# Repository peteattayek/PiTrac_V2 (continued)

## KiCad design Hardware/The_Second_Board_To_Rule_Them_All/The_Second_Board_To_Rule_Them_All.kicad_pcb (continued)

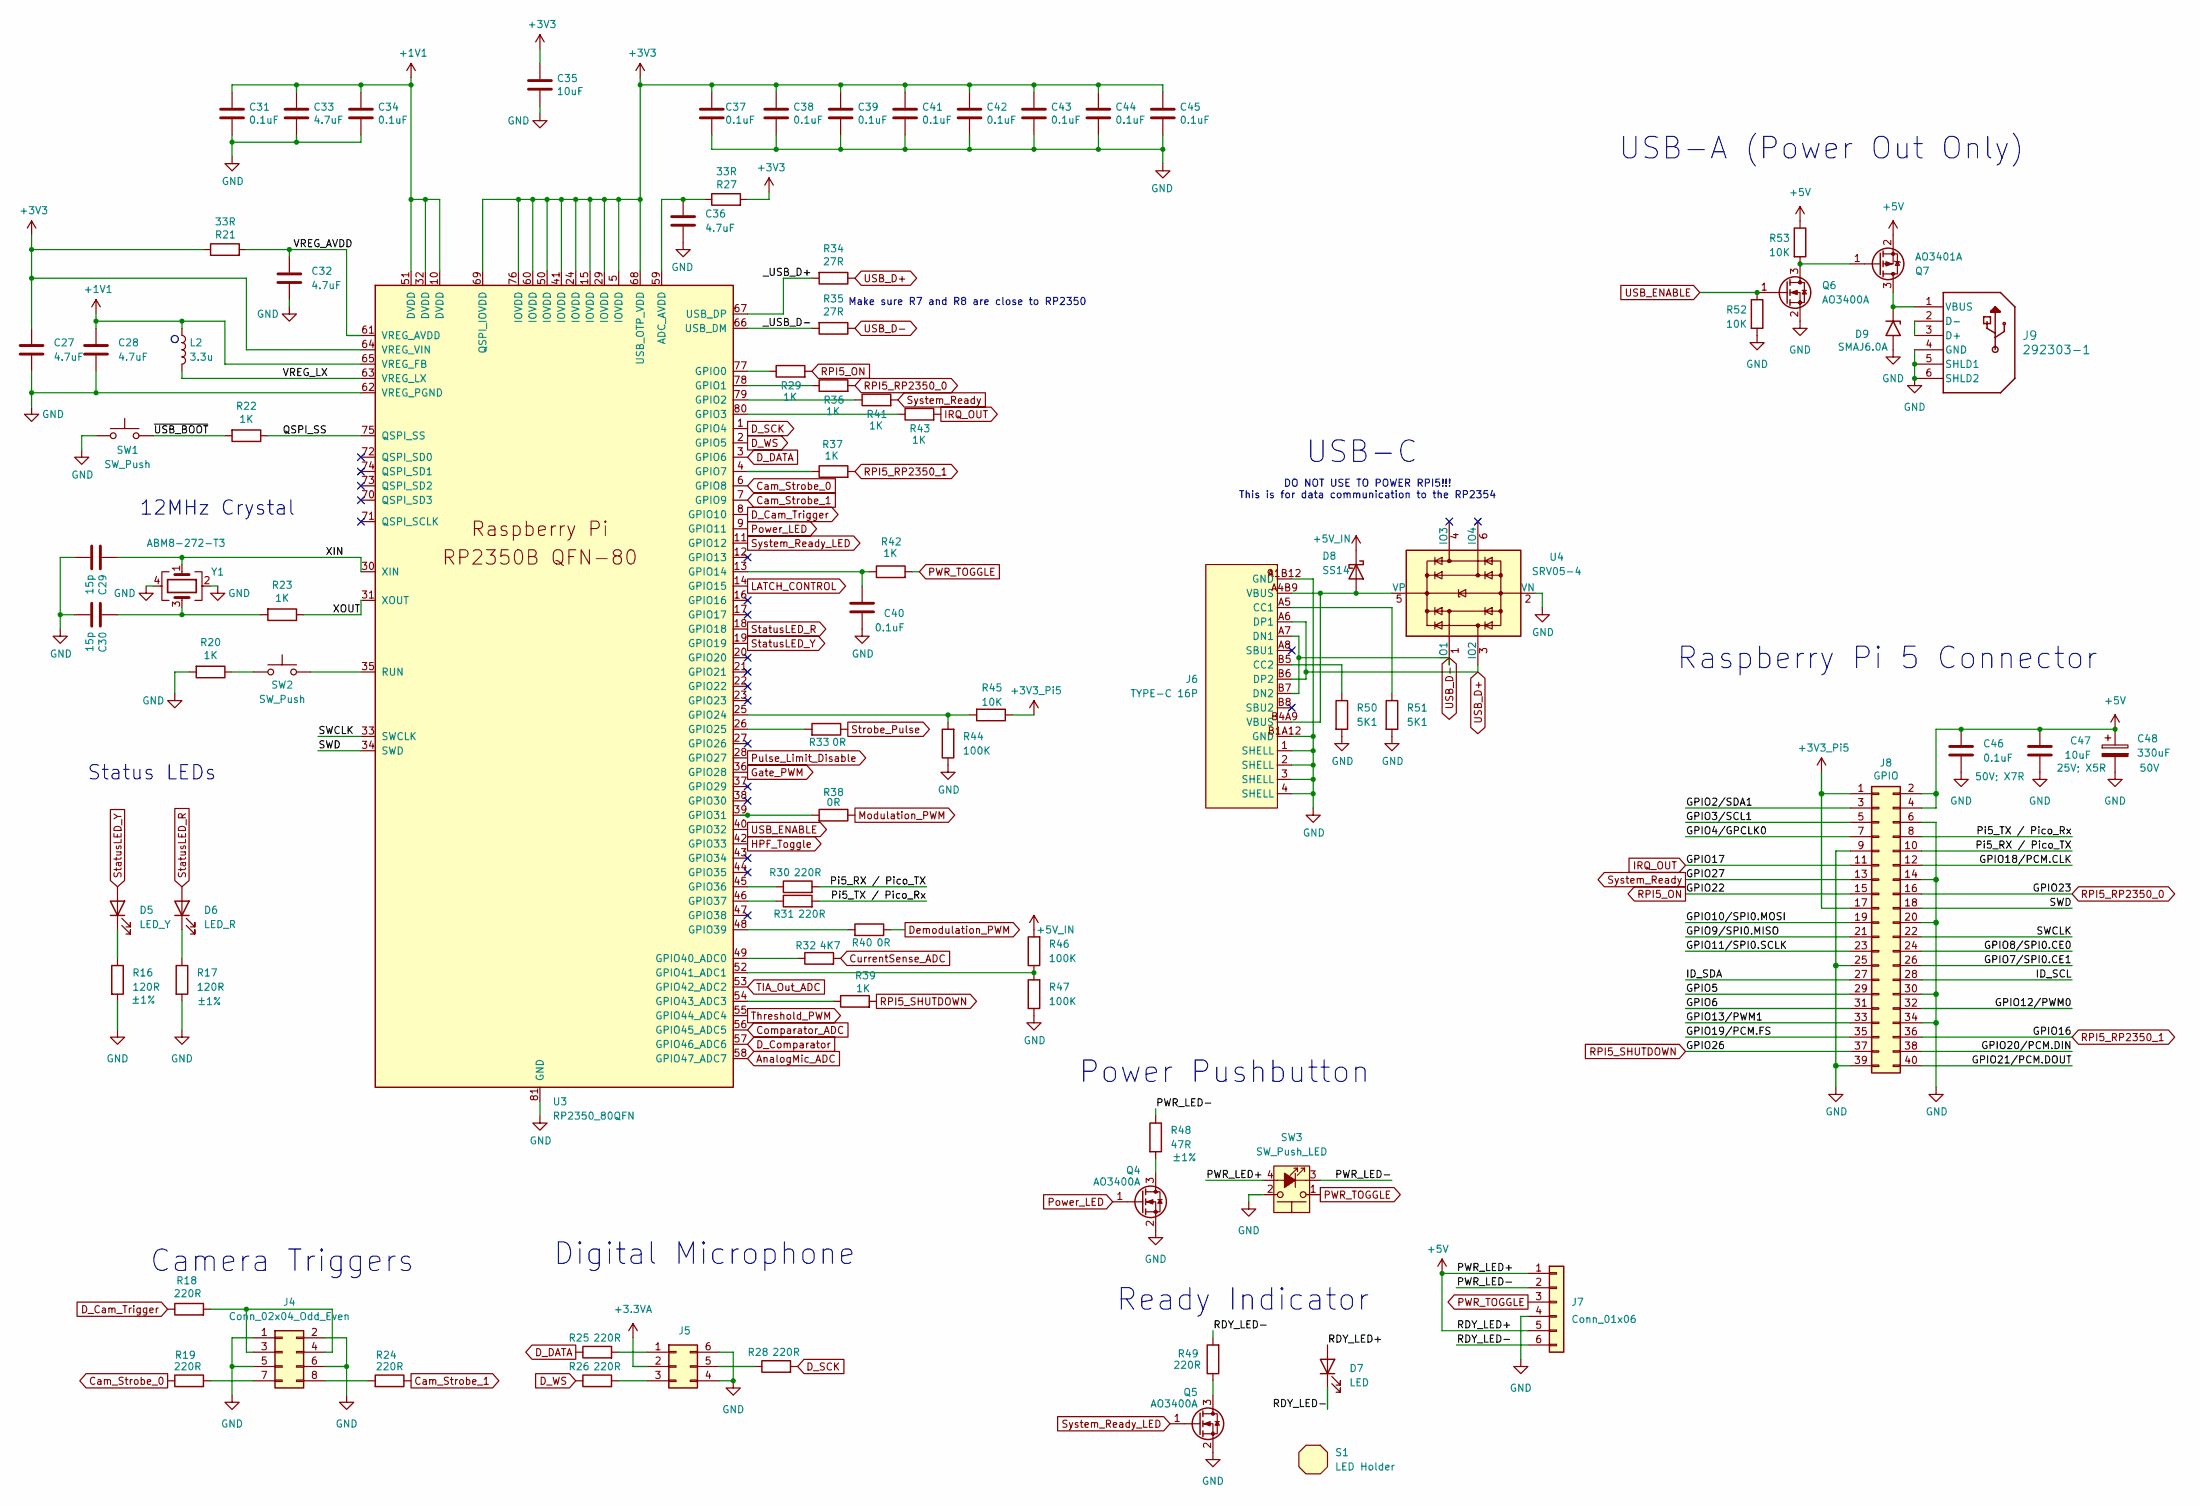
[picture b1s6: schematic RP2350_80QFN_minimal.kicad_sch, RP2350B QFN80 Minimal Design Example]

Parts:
C27, C28: 4.7uF; C_0402_1005Metric_small_pads; Ratings 10V; X5R; MPN CL05A475MP5NRNC; LCSC C23733
C29, C30: 15p; C_0402_1005Metric; Ratings C0G; MPN GRM1555C1H150JA01D; LCSC C1548
C31, C34, C37, C38, C39, C40, C41, C42, C43, C44, C45, C46: 0.1uF; C_0402_1005Metric; Ratings 50V; X7R; MPN CL05B104KB54PNC; LCSC C307331
C32, C33, C36: 4.7uF; C_0402_1005Metric; Ratings 10V; X5R; MPN CL05A475MP5NRNC; LCSC C23733
C35, C47: 10uF; C_0603_1608Metric; Ratings 25V; X5R; MPN CL10A106MA8NRNC; LCSC C96446
C48: 330uF; CAP_50TPV_10x10.5_RBY; Ratings 50V; MPN 50TPV330M10X10.5; LCSC C53120968
D5: LED_Y; LED_0603_1608Metric; MPN APT1608SYCK; LCSC C89811
D6: LED_R; LED_0603_1608Metric; MPN AA1608SURSK; LCSC C2286
D7: LED; MPN BL-BGE1V1
D8: SS14; D_SMA; MPN SS14; LCSC C2480
D9: SMAJ6.0A; D_SMA; MPN SMAJ6.0A; LCSC C19077525
J4: Conn_02x04_Odd_Even; PinHeader_2x04_P2.54mm_Vertical; MPN PH2-08-UA
J5: Conn_02x03_Counter_Clockwise; PinHeader_2x03_P2.54mm_Vertical; MPN PH2-06-UA
J6: TYPE-C 16P; USB-C-SMD_TYPE-C16PIN_C668624; MPN USB4105-GF-A; LCSC Part C668624
J7: Conn_01x06; PinHeader_1x06_P2.54mm_Vertical; MPN PH1-06-UA
J8: GPIO; PinSocket_2x20_P2.54mm_Vertical; MPN 16764
J9: 292303-1; CONN4_292303-1_TEC; MPN 292303-1
L2: 3.3u; L_pol_2016; MPN AOTA-B201610S3R3-101-T; LCSC C42411119
Q4, Q5: AO3400A; SOT-23; MPN AO3400A; LCSC C20917
Q6: AO3400A; SOT-23; MPN AO3400A; Digikey PN 785-1000-1-ND
Q7: AO3401A; SOT-23; MPN AO3401A; LCSC C15127
R16, R17: 120R; R_0402_1005Metric; Ratings ±1%; MPN RMCF0402FT120R; LCSC C25079
R18, R19, R24, R25, R26, R28, R30, R31, R49: 220R; R_0402_1005Metric; Ratings ±1%; MPN RMCF0402FT220R; LCSC C25091
R20, R22, R23, R29, R36, R37, R39, R41, R42, R43: 1K; R_0402_1005Metric; Ratings ±1%; MPN RMCF0402FT1K00; LCSC C11702
R21, R27: 33R; R_0402_1005Metric; Ratings ±1%; MPN RMCF0402FT33R0; LCSC C25105
R32: 4K7; R_1206_3216Metric; Ratings ±1% 1/4W; MPN RMCF1206FT4K70; LCSC C17936
R33, R38, R40: 0R; R_0805_2012Metric_Pad1.20x1.40mm_HandSolder; MPN RMCF0805ZT0R00; LCSC C17477
R34, R35: 27R; R_0603_1608Metric; Ratings ±1%; MPN RMCF0603FT27R0; LCSC C25190
R44, R46, R47: 100K; R_0402_1005Metric; Ratings ±1%; MPN RMCF0402FT100K; LCSC C25741
R45, R52, R53: 10K; R_0402_1005Metric; Ratings ±1%; MPN RMCF0402FT10K0; LCSC C25744
R48: 47R; R_0402_1005Metric; Ratings ±1%; MPN RMCF0402FT47R0; LCSC C25118
R50, R51: 5K1; R_0402_1005Metric; Ratings ±1%; MPN RMCF0402FT5K10; LCSC C25905
S1: LED Holder; MPN SSH-LXH501
SW1, SW2: SW_Push; SW_TS-1088_XNP; MPN TS-1088-AR02016; LCSC C720477
SW3: SW_Push_LED; MPN 481
U3: RP2350_80QFN; RP2350-QFN-80-1EP_10x10_P0.4mm_EP3.4x3.4mm_ThermalVias; MPN RP2354B; LCSC C39843328
U4: SRV05-4; SOT-23-6; MPN SRV05-4HTG-D; LCSC C7420376
Y1: ABM8-272-T3; Crystal_SMD_3225-4Pin_3.2x2.5mm; MPN ABM8-272-T3; LCSC C20625731

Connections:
+1V1: C28.1, C31.1, C33.1, C34.1, L2.1, U3.10 (DVDD), U3.32 (DVDD), U3.51 (DVDD), U3.65 (VREG_FB)
+3.3VA: J5.2; also elsewhere on the board
+3V3: C27.1, C35.1, C37.1, C38.1, C39.1, C41.1, C42.1, C43.1, C44.1, C45.1, R21.1, R27.2, U3.5 (IOVDD), U3.15 (IOVDD), U3.24 (IOVDD), U3.29 (IOVDD), U3.41 (IOVDD), U3.50 (IOVDD), U3.60 (IOVDD), U3.64 (VREG_VIN), U3.68 (USB_OTP_VDD), U3.69 (QSPI_IOVDD), U3.76 (IOVDD); also elsewhere on the board
+3V3_Pi5: J8.1, J8.17, R45.1
+5V: C46.2, C47.1, C48.1, D7.2 (A), J7.1, J7.5, J8.2, J8.4, Q7.2 (S), R53.1, SW3.4 (A); also elsewhere on the board
+5V_IN: D8.1 (K), R46.2; also elsewhere on the board
/MCU and Connectors/GPIO2/SDA1: J8.3
/MCU and Connectors/GPIO3/SCL1: J8.5
/MCU and Connectors/GPIO4/GPCLK0: J8.7
/MCU and Connectors/GPIO5: J8.29
/MCU and Connectors/GPIO6: J8.31
/MCU and Connectors/GPIO7/SPI0.CE1: J8.26
/MCU and Connectors/GPIO8/SPI0.CE0: J8.24
/MCU and Connectors/GPIO9/SPI0.MISO: J8.21
/MCU and Connectors/GPIO10/SPI0.MOSI: J8.19
/MCU and Connectors/GPIO11/SPI0.SCLK: J8.23
/MCU and Connectors/GPIO12/PWM0: J8.32
/MCU and Connectors/GPIO13/PWM1: J8.33
/MCU and Connectors/GPIO18/PCM.CLK: J8.12
/MCU and Connectors/GPIO19/PCM.FS: J8.35
/MCU and Connectors/GPIO20/PCM.DIN: J8.38
/MCU and Connectors/GPIO21/PCM.DOUT: J8.40
/MCU and Connectors/ID_SCL: J8.28
/MCU and Connectors/ID_SDA: J8.27
/MCU and Connectors/PWR_LED-: J7.2, R48.1, SW3.3 (K)
/MCU and Connectors/Pi5_RX / Pico_TX: J8.10, R30.2
/MCU and Connectors/Pi5_TX / Pico_Rx: J8.8, R31.2
/MCU and Connectors/QSPI_SS: R22.1, U3.75 (QSPI_SS)
/MCU and Connectors/RDY_LED-: D7.1 (K), J7.6, R49.2
/MCU and Connectors/SWCLK: J8.22, U3.33 (SWCLK)
/MCU and Connectors/SWD: J8.18, U3.34 (SWD)
/MCU and Connectors/VREG_AVDD: C32.1, R21.2, U3.61 (VREG_AVDD)
/MCU and Connectors/VREG_LX: L2.2, U3.63 (VREG_LX)
/MCU and Connectors/XIN: C29.1, U3.30 (XIN), Y1.1
/MCU and Connectors/XOUT: R23.1, U3.31 (XOUT)
/MCU and Connectors/_USB_D+: R34.2, U3.67 (USB_DP)
/MCU and Connectors/_USB_D-: R35.2, U3.66 (USB_DM)
/MCU and Connectors/~USB_BOOT: R22.2, SW1.2
AnalogMic_ADC: U3.58 (GPIO47_ADC7); also elsewhere on the board
Cam_Strobe_0: R19.1, U3.6 (GPIO8)
Cam_Strobe_1: R24.1, U3.7 (GPIO9)
Comparator_ADC: U3.56 (GPIO45_ADC5); also elsewhere on the board
CurrentSense_ADC: R32.2; also elsewhere on the board
D_Cam_Trigger: R18.1, U3.8 (GPIO10)
D_Comparator: U3.57 (GPIO46_ADC6); also elsewhere on the board
D_DATA: R25.1, U3.3 (GPIO6)
D_SCK: R28.2, U3.1 (GPIO4)
D_WS: R26.1, U3.2 (GPIO5)
Demodulation_PWM: R40.1; also elsewhere on the board
GND: C27.2, C28.2, C29.2, C30.2, C31.2, C32.2, C33.2, C34.2, C35.2, C36.2, C37.2, C38.2, C39.2, C40.1, C41.2, C42.2, C43.2, C44.2, C45.2, C46.1, C47.2, C48.2, D9.2 (A2), J4.1, J4.2, J4.5, J4.6, J5.4, J5.6, J6.1 (SHELL), J6.2 (SHELL), J6.3 (SHELL), J6.4 (SHELL), J6.A1B12 (GND), J6.B1A12 (GND), J7.4, J8.6, J8.9, J8.14, J8.20, J8.25, J8.30, J8.34, J8.39, J9.4 (GND), J9.5 (SHLD1), J9.6 (SHLD2), Q4.2 (S), Q5.2 (S), Q6.2 (S), R16.2, R17.2, R20.2, R44.1, R47.1, R50.2, R51.2, R52.2, SW1.1, SW3.2, U3.62 (VREG_PGND), U3.81 (GND), U4.2 (VN), Y1.2, Y1.4; also elsewhere on the board
Gate_PWM: U3.36 (GPIO28); also elsewhere on the board
HPF_Toggle: U3.42 (GPIO33); also elsewhere on the board
IRQ_OUT: J8.11, R43.2
LATCH_CONTROL: U3.14 (GPIO15); also elsewhere on the board
Modulation_PWM: R38.1; also elsewhere on the board
unnamed: C30.1, R23.2, Y1.3
unnamed: D5.1 (K), R16.1
unnamed: D6.1 (K), R17.1
unnamed: D8.2 (A), J6.A4B9 (VBUS), J6.B4A9 (VBUS), U4.5 (VP)
unnamed: D9.1 (A1), J9.1 (VBUS), Q7.3 (D)
unnamed: J4.3, J4.4, R18.2
unnamed: J4.7, R19.2
unnamed: J4.8, R24.2
unnamed: J5.1, R25.2
unnamed: J5.3, R26.2
unnamed: J5.5, R28.1
unnamed: J6.A5 (CC1), R51.1
unnamed: J6.B5 (CC2), R50.1
unnamed: J9.2 (D-), J9.3 (D+)
unnamed: Q4.3 (D), R48.2
unnamed: Q5.3 (D), R49.1
unnamed: Q6.3 (D), Q7.1 (G), R53.2
unnamed: R20.1, SW2.1
unnamed: C36.1, R27.1, U3.59 (ADC_AVDD)
unnamed: R29.1, U3.77 (GPIO0)
unnamed: R36.1, U3.78 (GPIO1)
unnamed: R41.1, U3.79 (GPIO2)
unnamed: R43.1, U3.80 (GPIO3)
unnamed: R37.1, U3.4 (GPIO7)
unnamed: C40.2, R42.1, U3.13 (GPIO14)
unnamed: R44.2, R45.2, U3.25 (GPIO24)
unnamed: R33.2, U3.26 (GPIO25)
unnamed: R38.2, U3.39 (GPIO31)
unnamed: R30.1, U3.45 (GPIO36)
unnamed: R31.1, U3.46 (GPIO37)
unnamed: R40.2, U3.48 (GPIO39)
unnamed: R32.1, U3.49 (GPIO40_ADC0)
unnamed: R46.1, R47.2, U3.52 (GPIO41_ADC1)
unnamed: R39.1, U3.54 (GPIO43_ADC3)
unnamed: SW2.2, U3.35 (RUN)
PWR_TOGGLE: J7.3, R42.2, SW3.1
Power_LED: Q4.1 (G), U3.9 (GPIO11)
Pulse_Limit_Disable: U3.28 (GPIO27); also elsewhere on the board
RPI5_ON: J8.15, R29.2
RPI5_RP2350_0: J8.16, R36.2
RPI5_RP2350_1: J8.36, R37.2
RPI5_SHUTDOWN: J8.37, R39.2
StatusLED_R: D6.2 (A), U3.18 (GPIO18)
StatusLED_Y: D5.2 (A), U3.19 (GPIO19)
Strobe_Pulse: R33.1; also elsewhere on the board
System_Ready: J8.13, R41.2
System_Ready_LED: Q5.1 (G), U3.11 (GPIO12)
TIA_Out_ADC: U3.53 (GPIO42_ADC2); also elsewhere on the board
Threshold_PWM: U3.55 (GPIO44_ADC4); also elsewhere on the board
USB_D+: J6.A6 (DP1), J6.B6 (DP2), R34.1, U4.3 (IO2)
USB_D-: J6.A7 (DN1), J6.B7 (DN2), R35.1, U4.1 (IO1)
USB_ENABLE: Q6.1 (G), R52.1, U3.40 (GPIO32)

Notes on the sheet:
12MHz Crystal
USB-C
DO NOT USE TO POWER RPI5!!! This is for data communication to the RP2354
Ready Indicator
Status LEDs
Camera Triggers
Digital Microphone
USB-A (Power Out Only)
Power Pushbutton
Raspberry Pi 5 Connector
Make sure R7 and R8 are close to RP2350

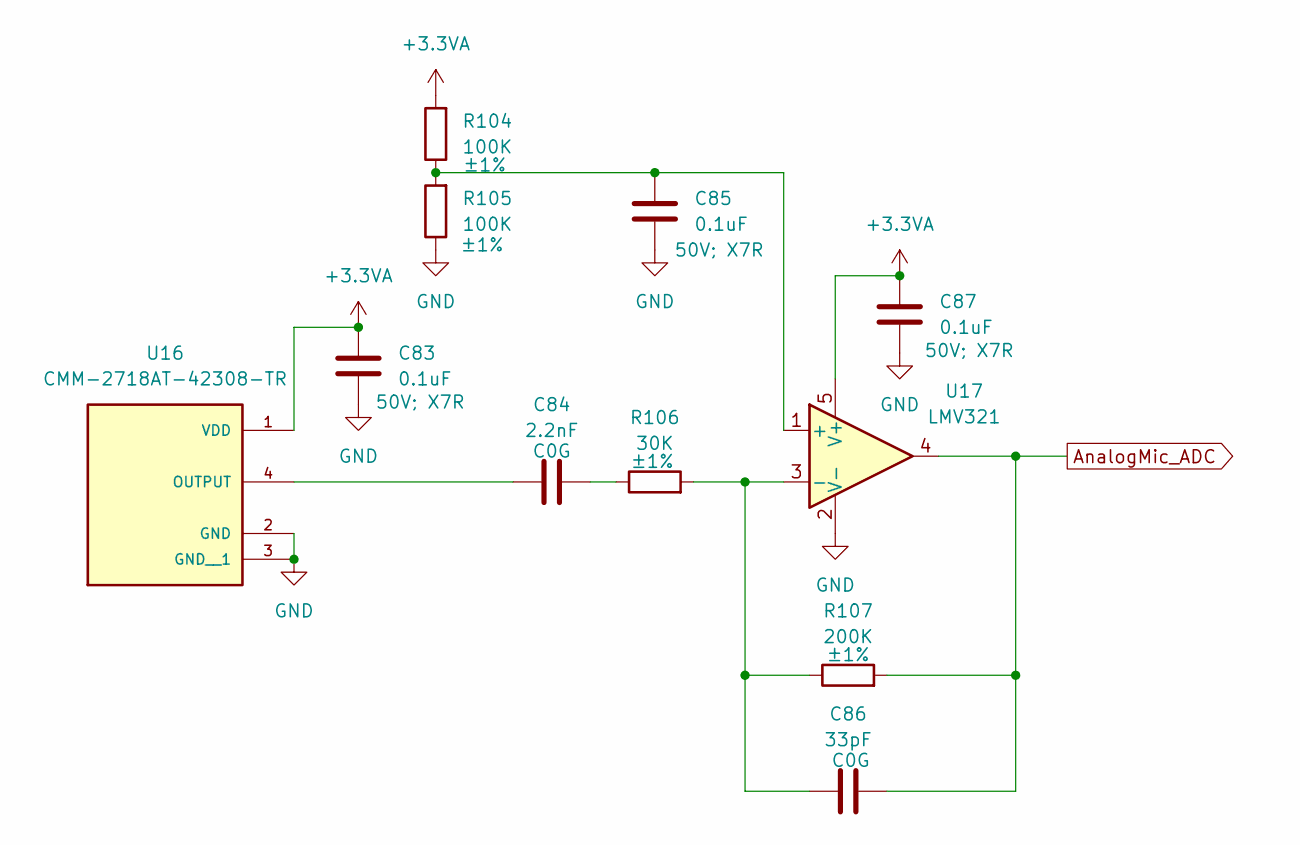
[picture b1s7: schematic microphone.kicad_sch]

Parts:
C83, C85, C87: 0.1uF; C_0402_1005Metric; Ratings 50V; X7R; MPN CL05B104KB54PNC; LCSC C307331
C84: 2.2nF; C_0805_2012Metric; Ratings C0G; MPN CL21C222JBFNNNE; LCSC C28260
C86: 33pF; C_0603_1608Metric; Ratings C0G; MPN CL10C330JB8NNNC; LCSC C1663
R104, R105: 100K; R_0402_1005Metric; Ratings ±1%; MPN RMCF0402FT100K; LCSC C25741
R106: 30K; R_0603_1608Metric; Ratings ±1%; MPN RMCF0603FT30K0; LCSC C22984
R107: 200K; R_0402_1005Metric; Ratings ±1%; MPN RMCF0402FT200K; LCSC C25764
U16: CMM-2718AT-42308-TR; XDCR_CMM-2718AT-42308-TR; MPN CMM-2718AT-42308-TR; LCSC C481300
U17: LMV321; SOT-23-5; MPN LMV321IDBVR; LCSC C7972

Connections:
+3.3VA: C83.2, C87.2, R104.2, U16.1 (VDD), U17.5 (V+); also elsewhere on the board
AnalogMic_ADC: C86.2, R107.2, U17.4; also elsewhere on the board
GND: C83.1, C85.1, C87.1, R105.1, U16.2 (GND), U16.3 (GND__1), U17.2 (V-); also elsewhere on the board
unnamed: C84.2, R106.1
unnamed: C84.1, U16.4 (OUTPUT)
unnamed: C85.2, R104.1, R105.2, U17.1 (+)
unnamed: C86.1, R106.2, R107.1, U17.3 (-)

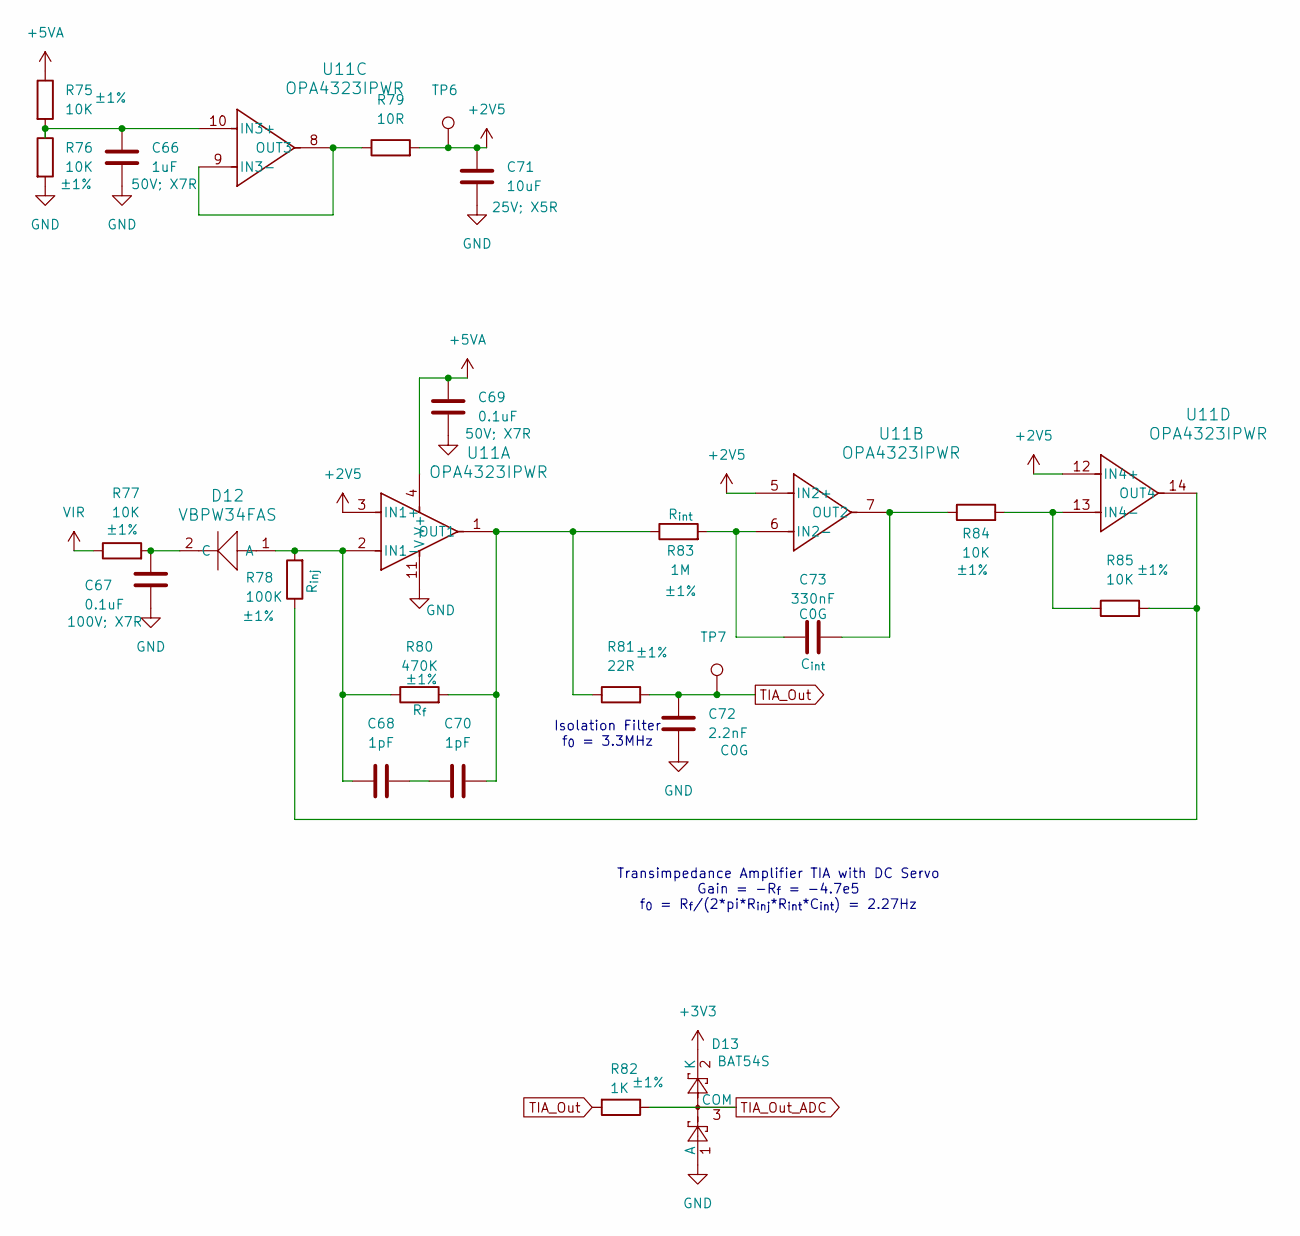
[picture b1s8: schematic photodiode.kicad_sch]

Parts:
C66: 1uF; C_0805_2012Metric; Ratings 50V; X7R; MPN CL21B105KBFNNNE; LCSC C28323
C67: 0.1uF; C_0805_2012Metric; Ratings 100V; X7R; MPN CL21B104KCFNNNE; LCSC C28233
C68, C70: 1pF; C_0402_1005Metric; Ratings C0G; MPN GRM1555C1H1R0BA01D; LCSC C1550
C69: 0.1uF; C_0402_1005Metric; Ratings 50V; X7R; MPN CL05B104KB54PNC; LCSC C307331
C71: 10uF; C_0603_1608Metric; Ratings 25V; X5R; MPN CL10A106MA8NRNC; LCSC C96446
C72: 2.2nF; C_0805_2012Metric; Ratings C0G; MPN CL21C222JBFNNNE; LCSC C28260
C73: 330nF; C_1206_3216Metric; Ratings C0G; MPN GRM31C5C1E334JE01L; LCSC C3837965
D12: VBPW34FAS; CR_W34FAS_VIS; MPN VBPW34FAS; LCSC C413453
D13: BAT54S; SOT-23; MPN BAT54SLT1G; LCSC C7420333
R75, R76, R77, R84, R85: 10K; R_0402_1005Metric; Ratings ±1%; MPN RMCF0402FT10K0; LCSC C25744
R78: 100K; R_0402_1005Metric; Ratings ±1%; MPN RMCF0402FT100K; LCSC C25741
R79: 10R; R_0402_1005Metric; Ratings ±1%; MPN RMCF0402FT10R0; LCSC C25077
R80: 470K; R_0603_1608Metric; Ratings ±1%; MPN RMCF0603FT470K; LCSC C23178
R81: 22R; R_0402_1005Metric; Ratings ±1%; MPN RMCF0402FT22R0; LCSC C25092
R82: 1K; R_0402_1005Metric; Ratings ±1%; MPN RMCF0402FT1K00; LCSC C11702
R83: 1M; R_0603_1608Metric; Ratings ±1%; MPN RMCF0603FT1M00; LCSC C22935
TP6, TP7: TestPoint; TestPoint_THTPad_D1.0mm_Drill0.5mm
U11: OPA4323IPWR; PW0014A-IPC_A; MPN OPA4323IPWR; LCSC C22419728

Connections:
+2V5: C71.1, R79.2, TP6.1 (1_1), U11.3 (IN1+), U11.5 (IN2+), U11.12 (IN4+); also elsewhere on the board
+3V3: D13.2 (K); also elsewhere on the board
+5VA: C69.1, R75.1, U11.4 (V+); also elsewhere on the board
GND: C66.2, C67.2, C69.2, C71.2, C72.2, D13.1 (A), R76.2, U11.11 (V-); also elsewhere on the board
unnamed: C68.1, C70.2
unnamed: C68.2, D12.1 (A), R78.2, R80.1, U11.2 (IN1-)
unnamed: C67.1, D12.2 (C), R77.2
unnamed: C70.1, R80.2, R81.1, R83.1, U11.1 (OUT1)
unnamed: C73.1, R83.2, U11.6 (IN2-)
unnamed: C73.2, R84.1, U11.7 (OUT2)
unnamed: C66.1, R75.2, R76.1, U11.10 (IN3+)
unnamed: R79.1, U11.8 (OUT3), U11.9 (IN3-)
unnamed: R84.2, R85.1, U11.13 (IN4-)
unnamed: R78.1, R85.2, U11.14 (OUT4)
TIA_Out: C72.1, R81.2, R82.2, TP7.1 (1_1); also elsewhere on the board
TIA_Out_ADC: D13.3 (COM), R82.1; also elsewhere on the board
VIR: R77.1; also elsewhere on the board

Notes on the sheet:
Isolation Filter f_{0} = 3.3MHz
Transimpedance Amplifier TIA with DC Servo Gain = -R_{f} = -4.7e5 f_{0} = R_{f}/(2*pi*R_{inj}*R_{int}*C_{int}) = 2.27Hz

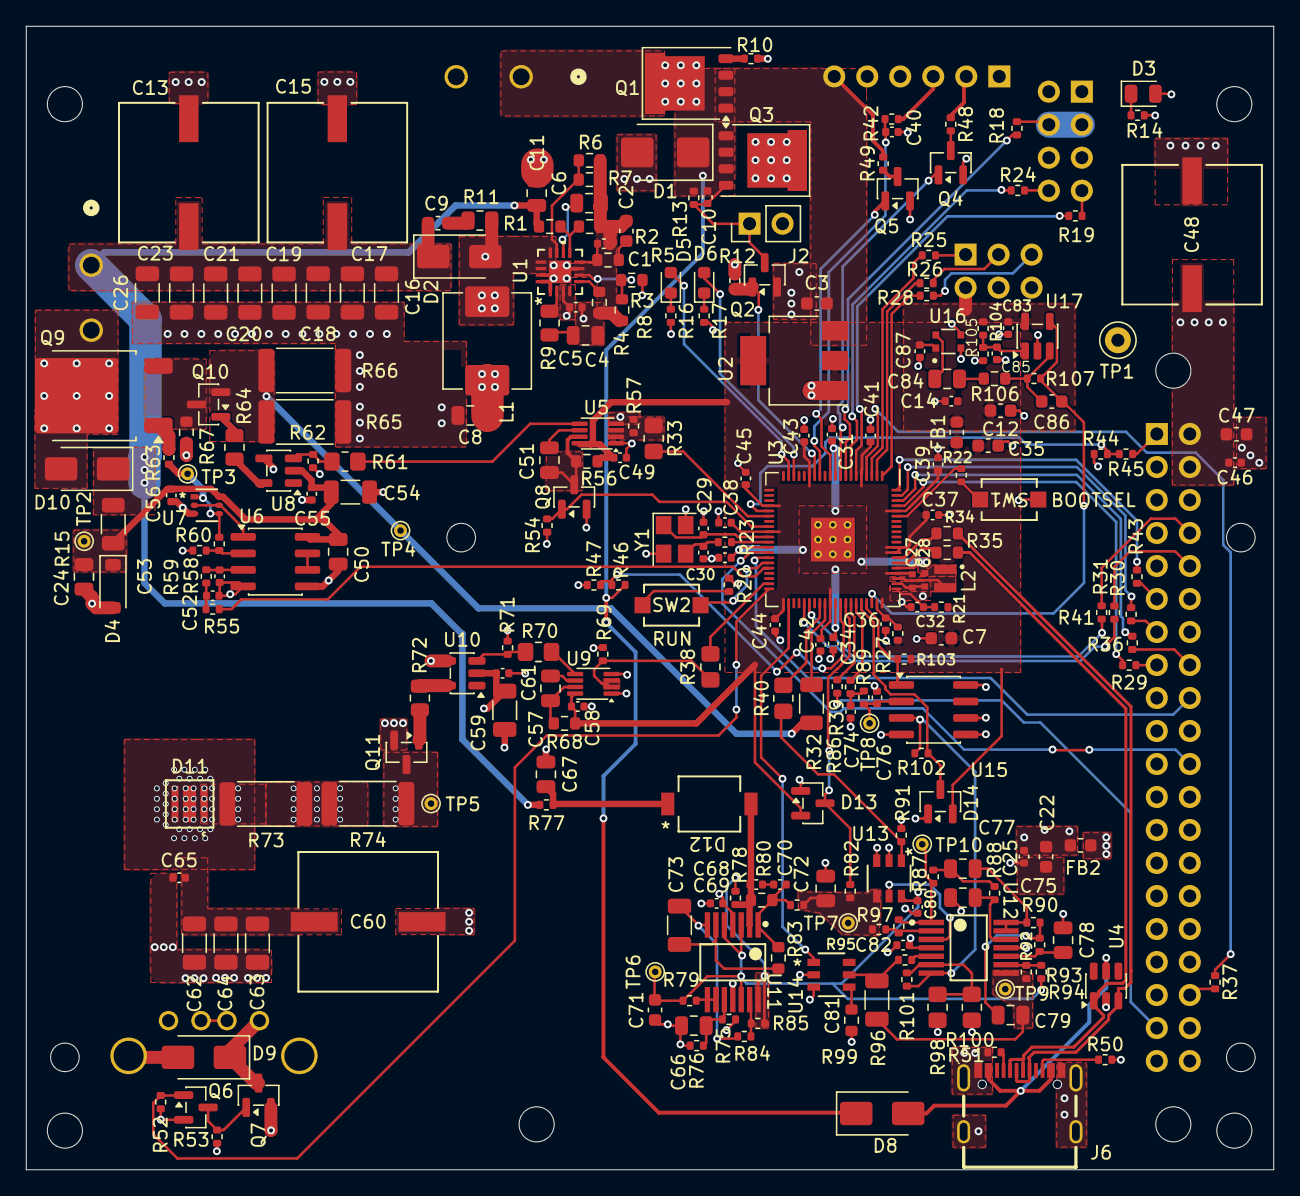
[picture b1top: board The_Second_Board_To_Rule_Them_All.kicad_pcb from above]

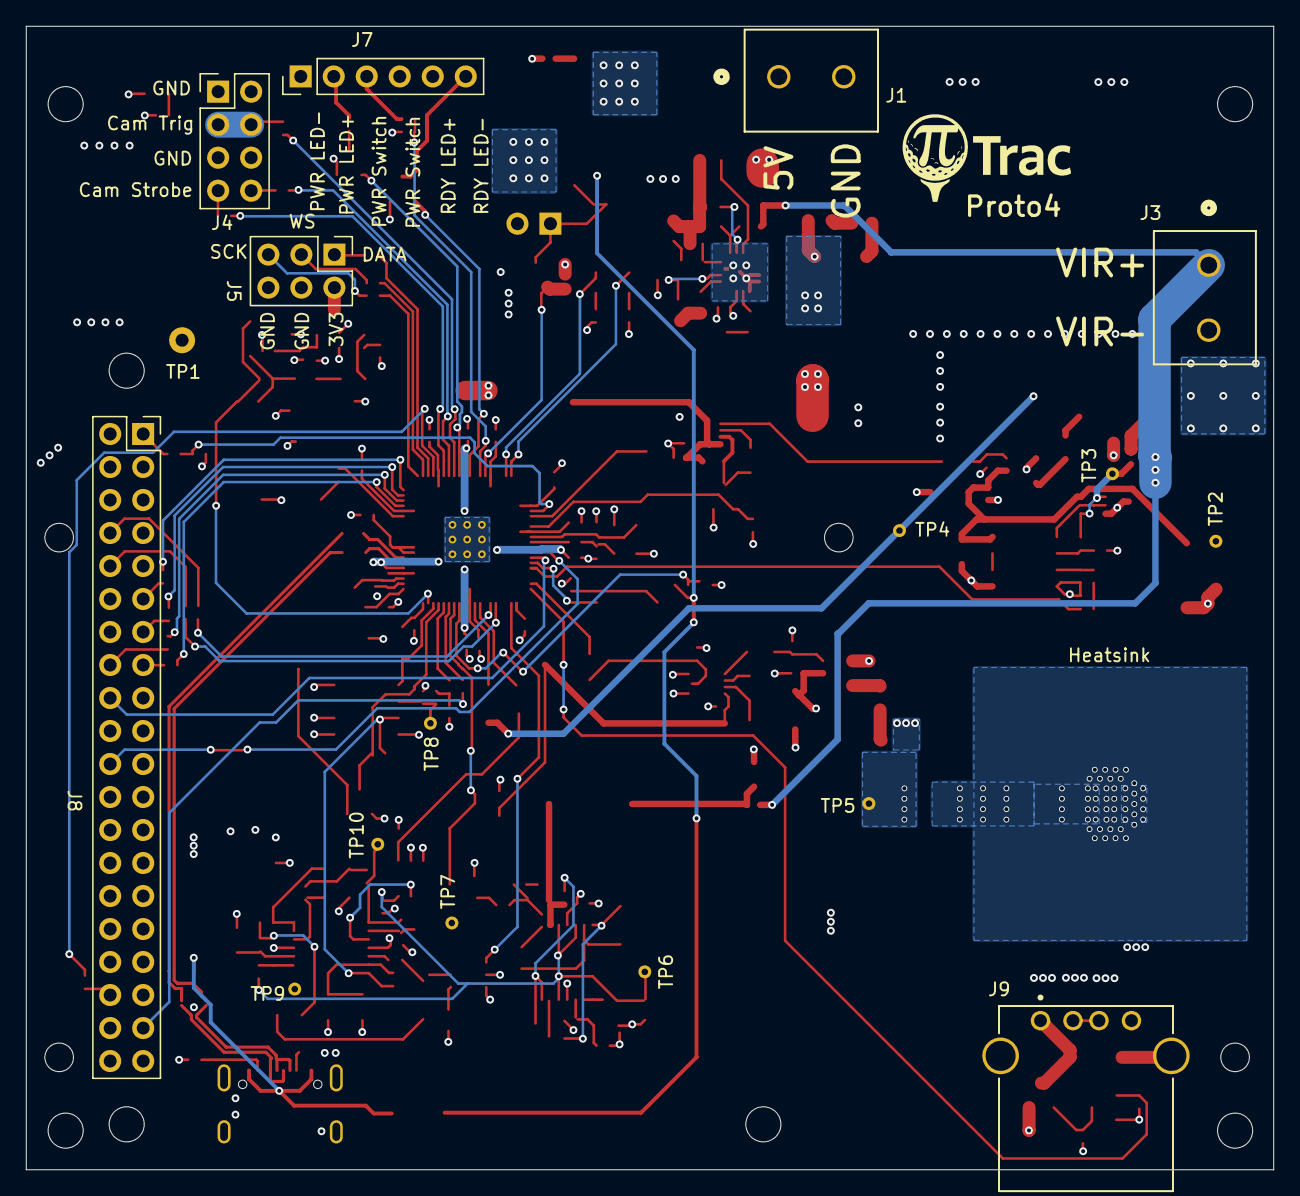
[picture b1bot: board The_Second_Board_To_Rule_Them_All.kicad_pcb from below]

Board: 4 copper layers, 96.0 x 88.0 mm, 273 parts (11 on the bottom side), 165 nets.

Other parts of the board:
MH1, MH2, MH4: MountingHole_2.7mm_M2.5

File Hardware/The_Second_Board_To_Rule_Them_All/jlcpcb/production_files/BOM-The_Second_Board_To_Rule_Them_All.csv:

Comment,Designator,Footprint,LCSC,Quantity
0.1uF,"C11,C50,C67",C_0805_2012Metric,C28233,3
0.1uF,"C10,C14,C25,C31,C34,C37,C38,C39,C40,C41,C42,C43,C44,C45,C46,C49,C5,C52,C53,C55,C56,C58,C61,C65,C69,C74,C76,C80,C82,C83,C85,C87",C_0402_1005Metric,C307331,32
0R,"R33,R38,R40,R61,R70",R_0805_2012Metric_Pad1.20x1.40mm_HandSolder,C17477,5
0R27,"R65,R66,R73,R74",R_2512_6332Metric,C2903472,4
1.5nF,C2,C_0603_1608Metric,C1595,1
100K,"R10,R104,R105,R44,R46,R47,R78",R_0402_1005Metric,C25741,7
10K,"R103,R12,R13,R45,R52,R53,R55,R58,R59,R75,R76,R77,R84,R85,R86,R89,R95,R97",R_0402_1005Metric,C25744,18
10R,R79,R_0402_1005Metric,C25077,1
10uF,C8,C_0805_2012Metric,C440198,1
10uF,"C12,C22,C3,C35,C47,C7,C71",C_0603_1608Metric,C96446,7
120R,"R16,R17",R_0402_1005Metric,C25079,2
12K,R3,R_0603_1608Metric,C22790,1
12V Zener,D4,D_SOD-123,C22395569,1
150K,R1,R_0603_1608Metric,C22807,1
15p,"C29,C30",C_0402_1005Metric,C1548,2
1K,"R102,R20,R22,R23,R29,R36,R37,R39,R41,R42,R43,R54,R57,R62,R69,R71,R82,R91,R99",R_0402_1005Metric,C11702,19
1M,R83,R_0603_1608Metric,C22935,1
1pF,"C68,C70",C_0402_1005Metric,C1550,2
1uF,"C24,C4,C6,C66",C_0805_2012Metric,C28323,4
2.2nF,"C51,C57,C72,C75,C77,C78,C79,C84",C_0805_2012Metric,C28260,8
2.2uF,"C16,C17,C18,C19,C20,C21,C23,C26",C_1206_3216Metric,C50254,8
200K,R107,R_0402_1005Metric,C25764,1
20K,R60,R_0402_1005Metric,C25765,1
20K,R8,R_0603_1608Metric,C4184,1
220R,"R14,R18,R19,R24,R25,R26,R28,R30,R31,R49",R_0402_1005Metric,C25091,10
22R,R81,R_0402_1005Metric,C25092,1
22uF,"C62,C63,C64",C_1206_3216Metric,C12891,3
27K,R101,R_0402_1005Metric,C25771,1
27R,"R34,R35",R_0603_1608Metric,C25190,2
2K,R100,R_0805_2012Metric_Pad1.20x1.40mm_HandSolder,C17604,1
2M,R96,R_0603_1608Metric,C22976,1
3.3u,L2,L_pol_2016,C42411119,1
30K,R106,R_0603_1608Metric,C22984,1
330nF,"C73,C81",C_1206_3216Metric,C3837965,2
330uF,"C13,C15,C48,C60",CAP_50TPV_10x10.5_RBY,C53120968,4
33R,"R21,R27",R_0402_1005Metric,C25105,2
33pF,C86,C_0603_1608Metric,C1663,1
4.7k,"R87,R88,R90,R92,R93,R94",R_0402_1005Metric,C25900,6
4.7pF,C1,C_0402_1005Metric,C1569,1
4.7uF,"C27,C28,C32,C33,C36",C_0402_1005Metric_small_pads,C23733,5
4.7uF,"C54,C59",C_1206_3216Metric,C29823,2
4.7uH,L1,L_Abracon_ASPI-0630LR,C207840,1
470K,R80,R_0603_1608Metric,C23178,1
47R,"R48,R63",R_0402_1005Metric,C25118,2
4K3,R2,R_0603_1608Metric,C23159,1
4K7,"R15,R32",R_1206_3216Metric,C17936,2
4R7,"R64,R72",R_0805_2012Metric,C17675,2
5.6K,R4,R_0603_1608Metric,C23189,1
510K,R5,R_0603_1608Metric,C23192,1
56K,"R56,R67,R68",R_0603_1608Metric,C23206,3
5K1,"R50,R51",R_0402_1005Metric,C25905,2
5R1,R9,R_0805_2012Metric,C17724,1
74LVC1G123,"U5,U9",VSSOP-8_2.3x2mm_P0.5mm,C26159250,2
75K,"R6,R7",R_0603_1608Metric,C23242,2
ABM8-272-T3,Y1,Crystal_SMD_3225-4Pin_3.2x2.5mm,C20625731,1
AO3400A,"Q10,Q11,Q2,Q4,Q5,Q6,Q8",SOT-23,C20917,7
AO3401A,Q7,SOT-23,C15127,1
BAT54S,"D13,D14",SOT-23,C7420333,2
CMM-2718AT-42308-TR,U16,XDCR_CMM-2718AT-42308-TR,C481300,1
FerriteBead,"FB1,FB2",L_0603_1608Metric,C14709,2
IRLR2905,Q9,ThermalVias,C3010,1
LED_G,D3,LED_0805_2012Metric,C2297,1
LED_R,D6,LED_0603_1608Metric,C2286,1
LED_Y,D5,LED_0603_1608Metric,C89811,1
LM358,U6,SOIC-8_3.9x4.9mm_P1.27mm,C7950,1
LM393,U15,SOIC-8_3.9x4.9mm_P1.27mm,C7955,1
LM5157RTER,U1,QFN_57RTER_TEX_ThermalVias,C5219222,1
LMV321,U17,SOT-23-5,C7972,1
MCP1416,"U10,U8",SOT-23-5,C83775,2
MMDT2227-7,U7,SOT-363_DIO,C41375117,1
NCP1117-3.3_SOT223,U2,SOT-223-3_TabPin2,C6186,1
OPA4323IPWR,"U11,U12",PW0014A-IPC_A,C22419728,2
RP2350_80QFN,U3,RP2350-QFN-80-1EP_10x10_P0.4mm_EP3.4x3.4mm_ThermalVias,C39843328,1
SI7137DP,"Q1,Q3",PQFN-8-EP_6x5mm_P1.27mm_Generic_ThermalVias,C42456927,2
SMAJ6.0A,D9,D_SMA,C19077525,1
SMBJ6.0A,D1,D_SMB,C19077560,1
SRV05-4,U4,SOT-23-6,C7420376,1
SS14,D8,D_SMA,C2480,1
SS26,"D10,D2",D_SMA,C7420363,2
SW_Push,"SW1,SW2",SW_TS-1088_XNP,C720477,2
TMUX1219DBVR,"U13,U14",SOT-23-6_DBV_TEX,C2869838,2
TYPE-C 16P,J6,USB-C-SMD_TYPE-C16PIN_C668624,C668624,1
VBPW34FAS,D12,CR_W34FAS_VIS,C413453,1
VSMA1085250x02,D11,DIODE_VSMA1085250_VIS,C20346087,1
